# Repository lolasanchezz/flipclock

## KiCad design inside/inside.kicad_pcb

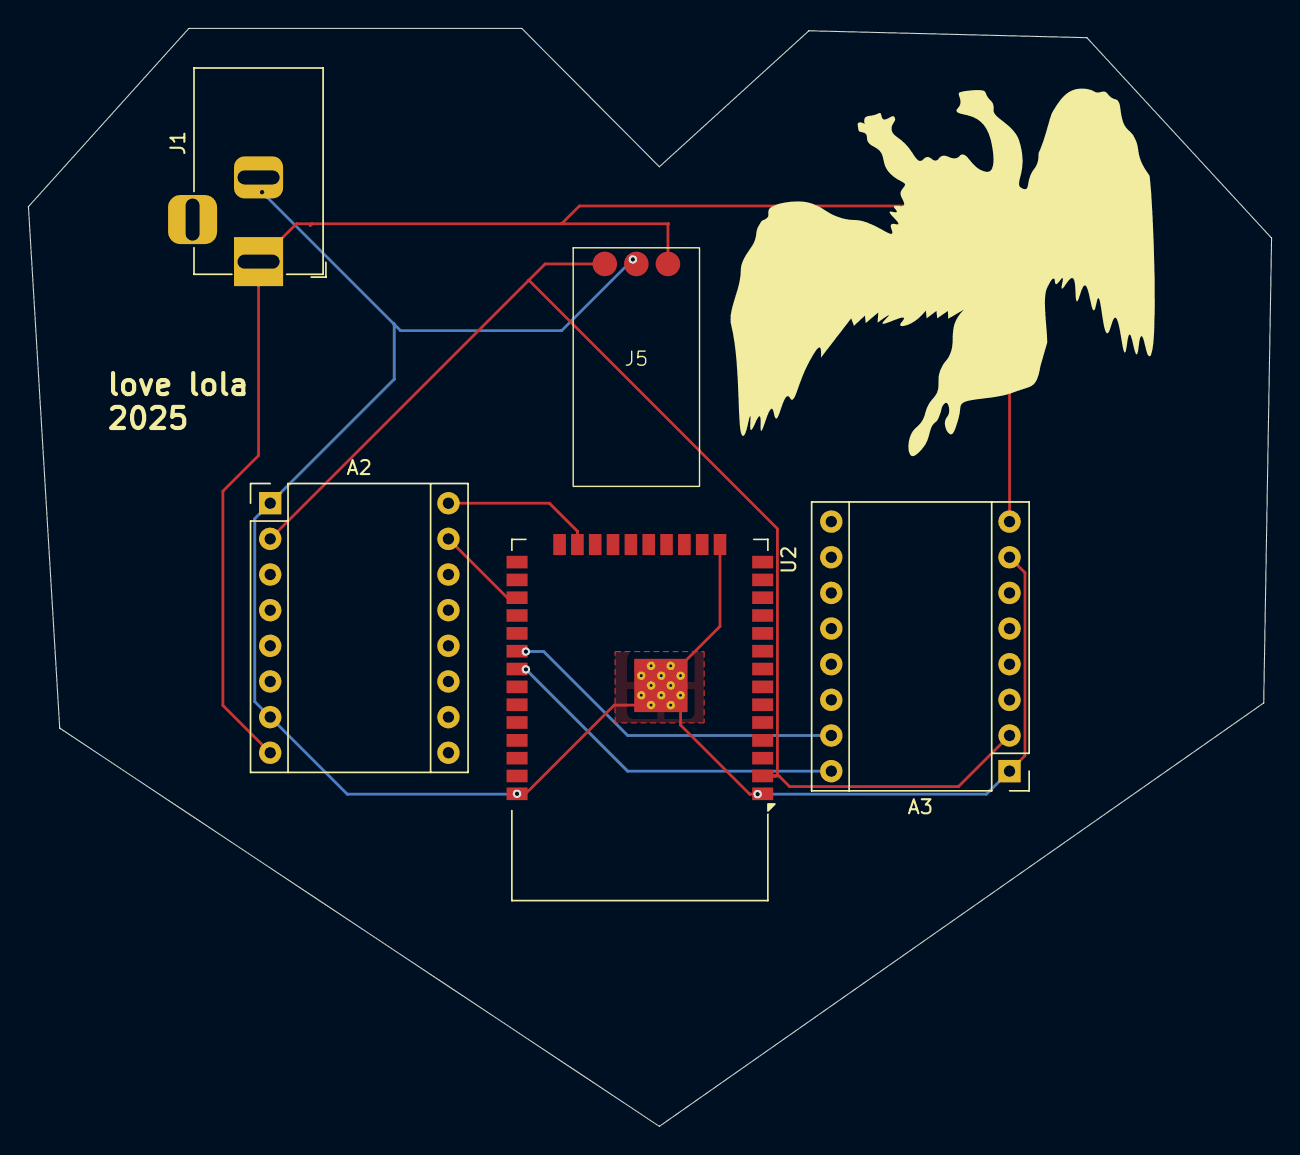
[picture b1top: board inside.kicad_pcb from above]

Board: 2 copper layers, 88.6 x 78.2 mm, 5 parts (0 on the bottom side), 7 nets.

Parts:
A2, A3: Pololu_Breakout_A4988; Pololu_Breakout-16_15.2x20.3mm
J1: Barrel_Jack; BarrelJack_Horizontal
J5: Conn_01x03; 1~5PCS EGBO DD4012SA 24v-12v
U2: ESP32-WROOM-32; ESP32-WROOM-32D

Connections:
GND: A2.1 (GND), A2.7 (GND), A3.1 (GND), A3.7 (GND), J1.2, J5.2, U2.1 (GND), U2.15 (GND), U2.38 (GND), U2.39 (GND)
unnamed: A2.16 (DIR), U2.23 (IO15)
unnamed: A2.15 (STEP), U2.27 (IO16)
unnamed: A2.2 (VDD), A3.2 (VDD), J5.1, U2.2 (VDD)
unnamed: A2.8 (VMOT), A3.8 (VMOT), J1.1, J5.3
unnamed: A3.16 (DIR), U2.31 (IO19)
unnamed: A3.15 (STEP), U2.30 (IO18)

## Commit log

2025-06-02 materials planning
2025-06-04 day 2 and 3
2025-06-05 svgs made
2025-06-12 finished pcb
2025-06-13 finished case
